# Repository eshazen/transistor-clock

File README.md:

# Incandescent Binary Clock

Crazy idea for a binary clock using small incandescent bulbs

Bulb count (20):

* (2) 10 Hours:  0-2      * *
* (4) 1 Hours    0-9  * * * *
* (3) 10 minutes 0-5    * * *
* (4) 1 minutes  0-9  * * * *
* (3) 10 seconds 0-5    * * *
* (4) 1 seconds  0-9  * * * *

To make it more interesting, let's build all the logic
out of discrete NPN and PNP transistors!

There's a schematic of a working 4-bit binary counter
with count=9 carry output and reset in `Spice/couter-4bit.asc`
(LTspice XVII format).

It requires "only" 18 transistors, 30 resistors, 12 capacitors.
So something like 150, 250, 100 total.

Maybe to make it reasonable to build make a counter "module"
PCB with two stages of 4-bit + 3-bit counter with jumper
options for divide-by 60, 12, 24.  Would need 4 of these on
some sort of motherboard.

Currently thinking to derive 60Hz from the AC line and provide
a buffered clock at this freq which drives all the other counters.

The spice version above is an example... would need to add an
enable input and the different divide-by options.

The 4-bit block requires about 40mA at -6V, so ~ 350mA for logic.
not counting the bulbs.  We could use e.g. 6.3V 150mA bulbs,
wit a total of 20 so ~3A if all bulbs lit.  So we need maybe
a -6V @ 5A total.

    0   0 0 0 0 0    0 0 0 0  0 0
    1   0 0 0 0 1    0 0 0 1  0 0
    2   0 0 0 1 0	 0 0 1 0  0 0
    3   0 0 0 1 1	 0 0 1 1  0 0
    4   0 0 1 0 0	 0 1 0 0  0 0
    5   0 0 1 0 1	 0 1 0 1  0 0
    6   0 0 1 1 0	 0 1 1 0  0 0
    7   0 0 1 1 1	 0 1 1 1  0 0
    8   0 1 0 0 0	 1 0 0 0  0 0
    9   0 1 0 0 1	 1 0 0 1  0 0
    
    10  0 1 0 1 0    0 0 0 0  0 1
    11  0 1 0 1 1    0 0 0 1  0 1
    12  0 1 1 0 0    0 0 1 0  0 1
    13  0 1 1 0 1    0 0 1 1  0 1
    14  0 1 1 1 0    0 1 0 0  0 1
    15  0 1 1 1 1    0 1 0 1  0 1
    16  1 0 0 0 0    0 1 1 0  0 1
    17  1 0 0 0 1    0 1 1 1  0 1
    18  1 0 0 1 0    1 0 0 0  0 1
    19  1 0 0 1 1    1 0 0 1  0 1
    
    20  1 0 1 0 0    0 0 0 0  1 0
    21  1 0 1 0 1    0 0 0 1  1 0
    22  1 0 1 1 0    0 0 1 0  1 0
    23  1 0 1 1 1    0 0 1 1  1 0
    
    24  1 1 0 0 0    0 1 0 0  1 0

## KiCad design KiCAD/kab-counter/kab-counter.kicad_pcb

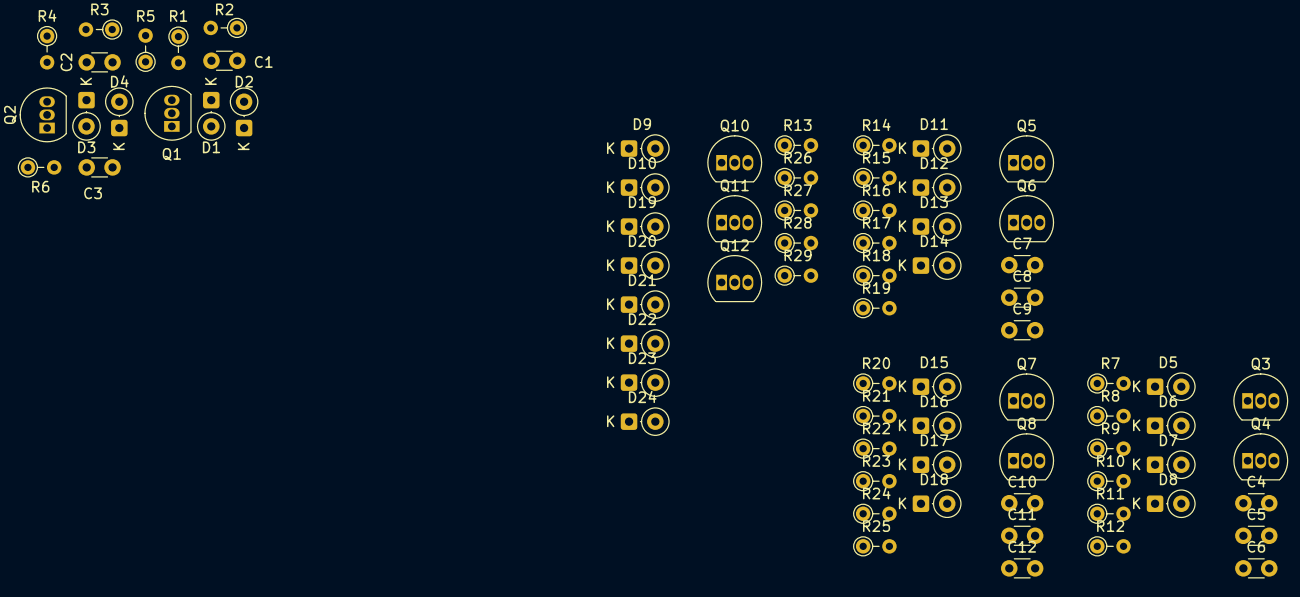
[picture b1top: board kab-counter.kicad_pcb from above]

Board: 2 copper layers, 76 parts (0 on the bottom side), 33 nets, no tracks yet.

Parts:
C1, C2, C3, C4, C5, C6, C7, C8, C9, C10, C11, C12: 220p; C_Disc_D3.0mm_W1.6mm_P2.50mm
D1, D2, D3, D4, D5, D6, D7, D8, D9, D10, D11, D12, D13, D14, D15, D16, D17, D18, D19, D20, D21, D22, D23, D24: 1N914; D_DO-35_SOD27_P2.54mm_Vertical_CathodeUp
Q1, Q2, Q3, Q4, Q5, Q6, Q7, Q8, Q11, Q12: 2N3904; TO-92_Inline
Q10: 2N3906; TO-92_Inline
R1, R4, R8, R12, R13, R15, R19, R21, R25, R26, R27, R28, R29: 10k; R_Axial_DIN0204_L3.6mm_D1.6mm_P2.54mm_Vertical
R2, R3, R5, R9, R10, R11, R16, R17, R18, R22, R23, R24: 100k; R_Axial_DIN0204_L3.6mm_D1.6mm_P2.54mm_Vertical
R6, R7, R14, R20: 1k; R_Axial_DIN0204_L3.6mm_D1.6mm_P2.54mm_Vertical

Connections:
+12V: Q11.3 (C), Q12.3 (C), R1.1, R4.1, R8.1, R12.1, R13.1, R15.1, R19.1, R21.1, R25.1, R27.1, R28.1, R29.1
/FF0/Q: C1.2, D9.1 (K), D23.1 (K), Q1.3 (C), R1.2, R2.2
/FF0/QN: C2.2, Q2.3 (C), R3.2, R4.2
/FF1/CK: D9.2 (A), D10.2 (A_2), R7.1, R13.2
/FF1/Q: C6.2, Q4.3 (C), R11.2, R12.2, R14.1
/FF1/QN: C5.2, Q3.3 (C), R8.2, R9.2
/FF2/Q: C9.2, D22.1 (K), Q6.3 (C), R18.2, R19.2
/FF2/QN: C8.2, Q5.3 (C), R15.2, R16.2
/FF3/CK: Q10.1 (E), R20.1, R27.2
/FF3/Q: C12.2, D24.1 (K), Q8.3 (C), R24.2, R25.2
/FF3/QN: C11.2, D21.1 (K), Q7.3 (C), R21.2, R22.2
GND: D2.2 (A), D3.2 (A), D6.2 (A), D7.2 (A), D12.2 (A), D13.2 (A), D16.2 (A), D17.2 (A), Q1.1 (E), Q2.1 (E), Q3.1 (E), Q4.1 (E), Q5.1 (E), Q6.1 (E), Q7.1 (E), Q8.1 (E), Q10.3 (C), R5.2, R10.2, R17.2, R23.2, R26.2
unnamed: C3.1, R6.2
unnamed: C4.1, R7.2
unnamed: C7.1, R14.2
unnamed: C10.1, R20.2
unnamed: C2.1, D1.2 (A), D2.1 (K), Q1.2 (B), R3.1
unnamed: C3.2, D1.1 (K), D4.1 (K), R5.1
unnamed: C1.1, D3.1 (K), D4.2 (A), Q2.2 (B), R2.1
unnamed: C6.1, D5.2 (A), D6.1 (K), Q3.2 (B), R11.1
unnamed: C4.2, D5.1 (K), D8.1 (K), R10.1
unnamed: C5.1, D7.1 (K), D8.2 (A), Q4.2 (B), R9.1
unnamed: C9.1, D11.2 (A), D12.1 (K), Q5.2 (B), R18.1
unnamed: C7.2, D11.1 (K), D14.1 (K), R17.1
unnamed: C8.1, D13.1 (K), D14.2 (A), Q6.2 (B), R16.1
unnamed: C12.1, D15.2 (A), D16.1 (K), Q7.2 (B), R24.1
unnamed: C10.2, D15.1 (K), D18.1 (K), R23.1
unnamed: C11.1, D17.1 (K), D18.2 (A), Q8.2 (B), R22.1
unnamed: D19.2 (A), Q11.1 (E)
unnamed: D19.1 (K), D20.1 (K), Q10.2 (B), R26.1
unnamed: D20.2 (A), Q12.1 (E)
unnamed: D21.2 (A), D22.2 (A), Q12.2 (B), R28.2
unnamed: D23.2 (A), D24.2 (A), Q11.2 (B), R29.2

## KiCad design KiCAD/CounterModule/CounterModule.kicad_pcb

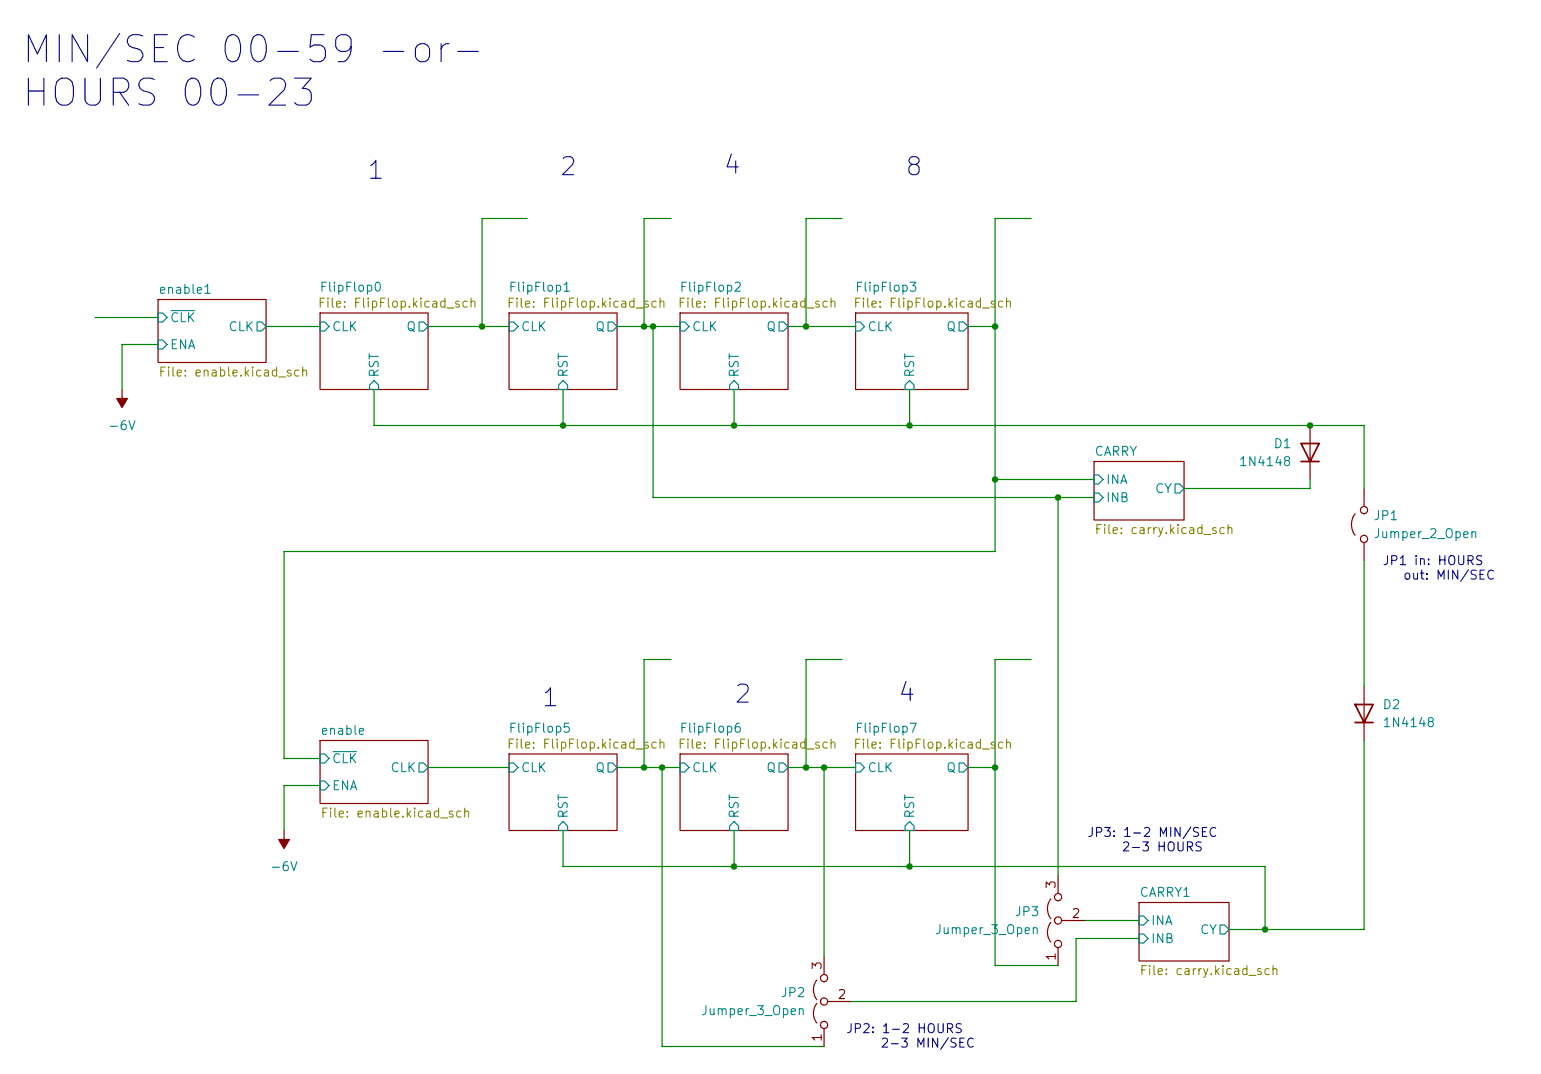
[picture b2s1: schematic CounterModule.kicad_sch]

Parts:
D1, D2: 1N4148; D_DO-35_SOD27_P7.62mm_Horizontal
JP1: Jumper_2_Open; PinHeader_1x02_P2.54mm_Vertical
JP2, JP3: Jumper_3_Open; PinHeader_1x03_P2.54mm_Vertical

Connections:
/CARRY1/CY: D2.1 (K); also elsewhere on the board
/CARRY1/INA: JP3.2 (C); also elsewhere on the board
/CARRY1/INB: JP2.2 (C); also elsewhere on the board
/CARRY/CY: D1.1 (K); also elsewhere on the board
/CARRY/INB: JP3.3 (B); also elsewhere on the board
/FlipFlop0/RST: D1.2 (A), JP1.2 (B); also elsewhere on the board
/FlipFlop5/Q: JP2.1 (A); also elsewhere on the board
/FlipFlop6/Q: JP2.3 (B); also elsewhere on the board
/FlipFlop7/Q: JP3.1 (A); also elsewhere on the board
unnamed: D2.2 (A), JP1.1 (A)

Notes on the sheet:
JP1 in: HOURS out: MIN/SEC
JP2: 1-2 HOURS 2-3 MIN/SEC
MIN/SEC 00-59 -or- HOURS 00-23
JP3: 1-2 MIN/SEC 2-3 HOURS

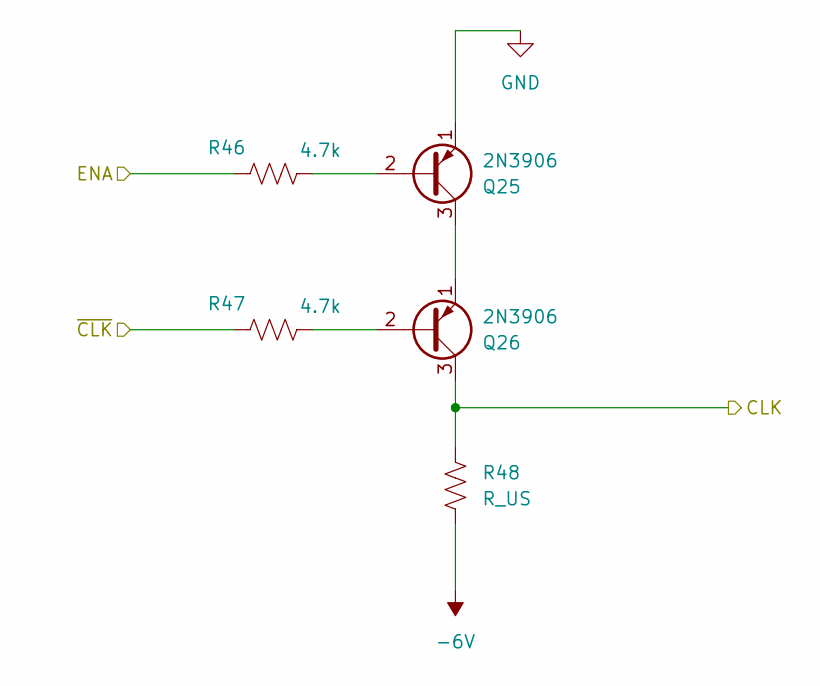
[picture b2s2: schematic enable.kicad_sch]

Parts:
Q25, Q26: 2N3906; TO-92_Inline
R46, R47: 4.7k; R_Axial_DIN0204_L3.6mm_D1.6mm_P2.54mm_Vertical
R48: R_US; R_Axial_DIN0204_L3.6mm_D1.6mm_P2.54mm_Vertical

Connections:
-6V: R46.1, R48.2; also elsewhere on the board
/FlipFlop0/CLK: Q26.3 (C), R48.1; also elsewhere on the board
/enable1/~CLK: R47.1
GND: Q25.1 (E); also elsewhere on the board
unnamed: Q25.2 (B), R46.2
unnamed: Q25.3 (C), Q26.1 (E)
unnamed: Q26.2 (B), R47.2

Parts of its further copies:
Q23, Q24: 2N3906; TO-92_Inline
R43, R44: 4.7k; R_Axial_DIN0204_L3.6mm_D1.6mm_P2.54mm_Vertical
R45: R_US; R_Axial_DIN0204_L3.6mm_D1.6mm_P2.54mm_Vertical

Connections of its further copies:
-6V: R43.1, R45.2; also elsewhere on the board
/CARRY/INA: R44.1; also elsewhere on the board
/FlipFlop5/CLK: Q24.3 (C), R45.1; also elsewhere on the board
GND: Q23.1 (E); also elsewhere on the board
unnamed: Q23.2 (B), R43.2
unnamed: Q23.3 (C), Q24.1 (E)
unnamed: Q24.2 (B), R44.2

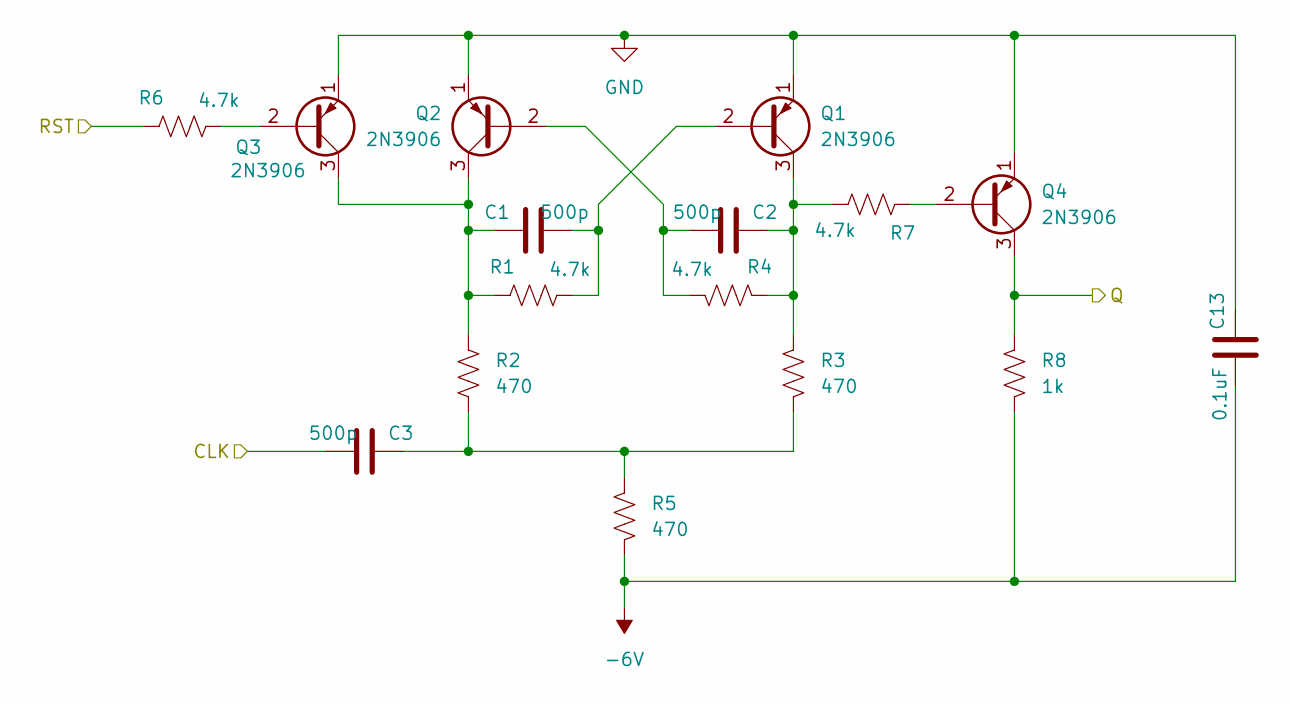
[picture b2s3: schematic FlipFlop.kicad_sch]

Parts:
C1, C2, C3: 500p; C_Disc_D4.3mm_W1.9mm_P5.00mm
C13: 0.1uF; C_Disc_D4.3mm_W1.9mm_P5.00mm
Q1, Q2, Q3, Q4: 2N3906; TO-92_Inline
R1, R4, R6, R7: 4.7k; R_Axial_DIN0204_L3.6mm_D1.6mm_P2.54mm_Vertical
R2, R3, R5: 470; R_Axial_DIN0204_L3.6mm_D1.6mm_P2.54mm_Vertical
R8: 1k; R_Axial_DIN0204_L3.6mm_D1.6mm_P2.54mm_Vertical

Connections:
-6V: C13.2, R5.2, R8.2; also elsewhere on the board
/FlipFlop0/CLK: C3.2; also elsewhere on the board
/FlipFlop0/Q: Q4.3 (C), R8.1; also elsewhere on the board
/FlipFlop0/RST: R6.1; also elsewhere on the board
GND: C13.1, Q1.1 (E), Q2.1 (E), Q3.1 (E), Q4.1 (E); also elsewhere on the board
unnamed: C3.1, R2.2, R3.2, R5.1
unnamed: C1.2, Q1.2 (B), R1.2
unnamed: C2.1, Q1.3 (C), R3.1, R4.1, R7.2
unnamed: C2.2, Q2.2 (B), R4.2
unnamed: C1.1, Q2.3 (C), Q3.3 (C), R1.1, R2.1
unnamed: Q3.2 (B), R6.2
unnamed: Q4.2 (B), R7.1

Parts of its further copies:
C4, C5, C6, C7, C8, C9, C10, C11, C12, C16, C17, C18, C19, C20, C21, C22, C23, C24: 500p; C_Disc_D4.3mm_W1.9mm_P5.00mm
C14, C15, C25, C26, C27, C28: 0.1uF; C_Disc_D4.3mm_W1.9mm_P5.00mm
Q5, Q6, Q7, Q8, Q9, Q10, Q11, Q12, Q13, Q14, Q15, Q16, Q27, Q28, Q29, Q30, Q31, Q32, Q33, Q34, Q35, Q36, Q37, Q38: 2N3906; TO-92_Inline
R9, R11, R13, R15, R17, R19, R21, R23, R25, R27, R29, R31, R51, R52, R53, R54, R59, R60, R61, R62, R67, R68, R69, R70: 4.7k; R_Axial_DIN0204_L3.6mm_D1.6mm_P2.54mm_Vertical
R10, R12, R14, R18, R20, R22, R26, R28, R30, R55, R56, R58, R63, R64, R66, R71, R72, R74: 470; R_Axial_DIN0204_L3.6mm_D1.6mm_P2.54mm_Vertical
R16, R24, R32, R57, R65, R73: 1k; R_Axial_DIN0204_L3.6mm_D1.6mm_P2.54mm_Vertical

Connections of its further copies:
-6V: C14.2, C15.2, C25.2, C26.2, C27.2, C28.2, R12.2, R16.2, R20.2, R24.2, R28.2, R32.2, R57.2, R58.2, R65.2, R66.2, R73.2, R74.2; also elsewhere on the board
/CARRY1/CY: R51.1, R59.1, R67.1; also elsewhere on the board
/CARRY/INA: Q16.3 (C), R32.1; also elsewhere on the board
/CARRY/INB: C7.2, Q8.3 (C), R16.1; also elsewhere on the board
/FlipFlop0/Q: C4.2; also elsewhere on the board
/FlipFlop0/RST: R9.1, R17.1, R25.1; also elsewhere on the board
/FlipFlop2/Q: C10.2, Q12.3 (C), R24.1
/FlipFlop5/CLK: C18.2; also elsewhere on the board
/FlipFlop5/Q: C21.2, Q30.3 (C), R57.1; also elsewhere on the board
/FlipFlop6/Q: C24.2, Q34.3 (C), R65.1; also elsewhere on the board
/FlipFlop7/Q: Q38.3 (C), R73.1; also elsewhere on the board
GND: C14.1, C15.1, C25.1, C26.1, C27.1, C28.1, Q5.1 (E), Q6.1 (E), Q7.1 (E), Q8.1 (E), Q9.1 (E), Q10.1 (E), Q11.1 (E), Q12.1 (E), Q13.1 (E), Q14.1 (E), Q15.1 (E), Q16.1 (E), Q27.1 (E), Q28.1 (E), Q29.1 (E), Q30.1 (E), Q31.1 (E), Q32.1 (E), Q33.1 (E), Q34.1 (E), Q35.1 (E), Q36.1 (E), Q37.1 (E), Q38.1 (E); also elsewhere on the board
unnamed: C4.1, R10.2, R12.1, R14.2
unnamed: C7.1, R18.2, R20.1, R22.2
unnamed: C10.1, R26.2, R28.1, R30.2
unnamed: C18.1, R55.2, R56.2, R58.1
unnamed: C21.1, R63.2, R64.2, R66.1
unnamed: C24.1, R71.2, R72.2, R74.1
unnamed: Q5.2 (B), R9.2
unnamed: C5.1, Q5.3 (C), Q6.3 (C), R10.1, R11.1
unnamed: C6.2, Q6.2 (B), R13.2
unnamed: C5.2, Q7.2 (B), R11.2
unnamed: C6.1, Q7.3 (C), R13.1, R14.1, R15.2
unnamed: Q8.2 (B), R15.1
unnamed: Q9.2 (B), R17.2
unnamed: C9.2, Q10.2 (B), R21.2
unnamed: C8.1, Q9.3 (C), Q10.3 (C), R18.1, R19.1
unnamed: C8.2, Q11.2 (B), R19.2
unnamed: C9.1, Q11.3 (C), R21.1, R22.1, R23.2
unnamed: Q12.2 (B), R23.1
unnamed: Q13.2 (B), R25.2
unnamed: C11.1, Q13.3 (C), Q14.3 (C), R26.1, R27.1
unnamed: C12.2, Q14.2 (B), R29.2
unnamed: C11.2, Q15.2 (B), R27.2
unnamed: C12.1, Q15.3 (C), R29.1, R30.1, R31.2
unnamed: Q16.2 (B), R31.1
unnamed: Q27.2 (B), R51.2
unnamed: C16.1, Q27.3 (C), Q28.3 (C), R53.1, R55.1
unnamed: C17.2, Q28.2 (B), R54.2
unnamed: C16.2, Q29.2 (B), R53.2
unnamed: C17.1, Q29.3 (C), R52.2, R54.1, R56.1
unnamed: Q30.2 (B), R52.1
unnamed: Q31.2 (B), R59.2
unnamed: C19.1, Q31.3 (C), Q32.3 (C), R61.1, R63.1
unnamed: C20.2, Q32.2 (B), R62.2
unnamed: C19.2, Q33.2 (B), R61.2
unnamed: C20.1, Q33.3 (C), R60.2, R62.1, R64.1
unnamed: Q34.2 (B), R60.1
unnamed: Q35.2 (B), R67.2
unnamed: C22.1, Q35.3 (C), Q36.3 (C), R69.1, R71.1
unnamed: C23.2, Q36.2 (B), R70.2
unnamed: C22.2, Q37.2 (B), R69.2
unnamed: C23.1, Q37.3 (C), R68.2, R70.1, R72.1
unnamed: Q38.2 (B), R68.1

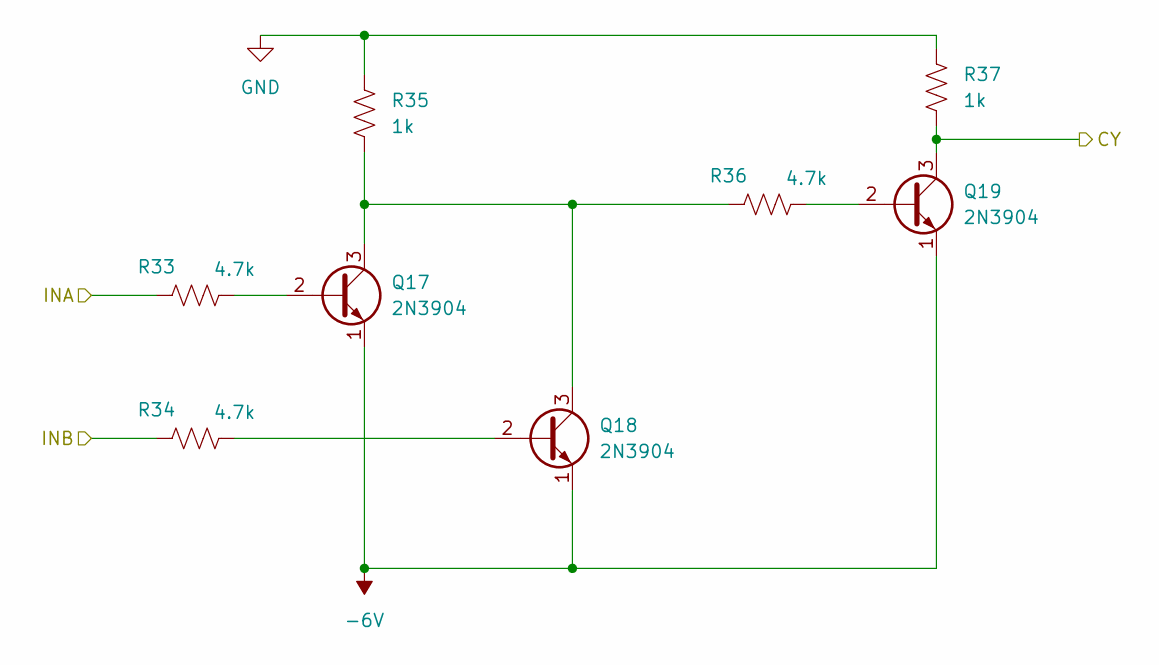
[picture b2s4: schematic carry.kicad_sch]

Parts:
Q17, Q18, Q19: 2N3904; TO-92_Inline
R33, R34, R36: 4.7k; R_Axial_DIN0204_L3.6mm_D1.6mm_P2.54mm_Vertical
R35, R37: 1k; R_Axial_DIN0204_L3.6mm_D1.6mm_P2.54mm_Vertical

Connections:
-6V: Q17.1 (E), Q18.1 (E), Q19.1 (E); also elsewhere on the board
/CARRY/CY: Q19.3 (C), R37.2; also elsewhere on the board
/CARRY/INA: R33.1; also elsewhere on the board
/CARRY/INB: R34.1; also elsewhere on the board
GND: R35.1, R37.1; also elsewhere on the board
unnamed: Q17.2 (B), R33.2
unnamed: Q17.3 (C), Q18.3 (C), R35.2, R36.1
unnamed: Q18.2 (B), R34.2
unnamed: Q19.2 (B), R36.2

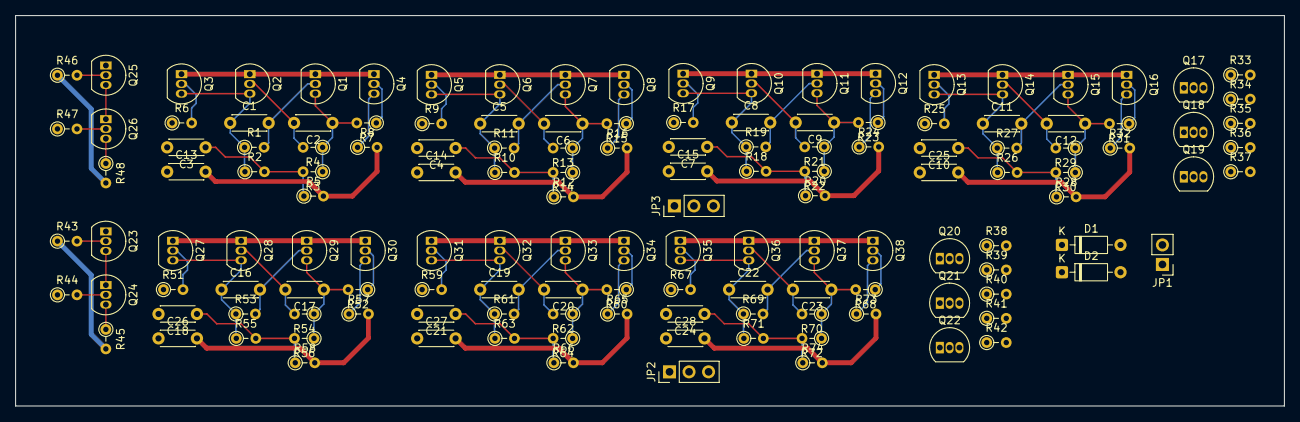
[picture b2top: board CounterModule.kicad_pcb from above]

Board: 2 copper layers, 165.1 x 50.8 mm, 143 parts (0 on the bottom side), 80 nets.

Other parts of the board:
Q20, Q21, Q22: 2N3904; TO-92_Inline
R38, R39: 1k; R_Axial_DIN0204_L3.6mm_D1.6mm_P2.54mm_Vertical
R40, R41, R42: 4.7k; R_Axial_DIN0204_L3.6mm_D1.6mm_P2.54mm_Vertical

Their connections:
-6V: Q20.1 (E), Q21.1 (E), Q22.1 (E); also elsewhere on the board
/CARRY1/CY: Q20.3 (C), R38.2; also elsewhere on the board
/CARRY1/INA: R41.1; also elsewhere on the board
/CARRY1/INB: R42.1; also elsewhere on the board
GND: R38.1, R39.1; also elsewhere on the board
unnamed: Q20.2 (B), R40.2
unnamed: Q21.2 (B), R41.2
unnamed: Q21.3 (C), Q22.3 (C), R39.2, R40.1
unnamed: Q22.2 (B), R42.2

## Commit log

2026-02-20 Initial diagrams
2026-02-22 working on counter
2026-02-26 working on 60x counter
2026-02-28 attempt at universal counter
2026-03-15 readme
2026-04-22 starting new FF
2026-04-22 starting on KAB ff
2026-04-22 clean up
2026-04-22 working on FF placement
